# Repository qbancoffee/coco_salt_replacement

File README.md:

# Drop in replacement board for the custom SALT chip on the CoCo's

- [Installation instructions](https://github.com/qbancoffee/coco_salt_replacement/wiki/Installing-a-pepper-board)
- [View PDF version of the schematic](pepper_schematic.pdf)
- [Download the latest release](https://github.com/qbancoffee/coco_salt_replacement/releases/latest)
- [How to order from JLCPCB](#Ordering-the-board)
- [Peppers in the wild](#Peppers-In-The-Wild)

This board replaces the functionality of the SALT chip in the CoCo (CoCo 2 in my case). 
The SALT chip (Supply and Level Translator) is responsible for supply regulation, RS-232
interface, level translation, cassette read operations, and driving the cassette relay.

I designed it using available parts from JLCPCB to reduce assembly time and to bring down the cost.

## Goals
- [x] Power regulation with a switching regulator instead of a linear regulator.
- [x] RS232 interface.
- [x] Zero crossing detector to read cassette data.
- [x] Cassette relay control.

All goals were met!!!<br>
[Video testing the SALT replacement board AKA the PEPPER board](https://youtu.be/D6V6HFp6FHY)

## Layout

## 3D rendering and pictures of it installed

<br>
<br>

<br>
CoCo 2 with SALT chip top view rendering

<br>
CoCo 2 with SALT chip side view rendering

## SALT and PEPPER

## Ordering the board
First Thing to do is clone this repository or download the latest release.
- [Download the latest release](https://github.com/qbancoffee/coco_salt_replacement/releases/latest)<br>
All the files you'll need are in the gerber folder.

Many PCB manufacturers provide proprietary EDA software with nice and helpful features to help the user decrease the time and difficulty when designing a PCB. Unfortunately sometimes these programs will only allow you to order from that specific manufacturer. This is good for the manufacturer because it increases the odds that the person will order from them again because of the amount of time invested in learning to use that specific EDA program.

There are very nice EDA programs that will allow to design a PCB really quickly with fewer errors when it comes to components and footprints. Some of these programs are free to download and use for a trial period but after finishing your design sometimes you'll find that in order to export your design files so that you can actually order the boards you have to purchase a license. Sometimes you'll also find that there is a total area limit on the size of your design unless you buy a license. Companies use these tactics to make money and I really can't blame them because they have to make a living somehow.

I guess the question you might be asking is "Is there a specific PCB manufacturer I must use for a PCB designed with KiCAD?" The answer is no.
PCB manufacturers will still take your business even if you've elected to use another piece of software for your design so long as you can provide the Gerber files for your design. The Gerber format is an open ASCII vector format for printed circuit board (PCB) designs. It is the de facto standard used by PCB industry software to describe the printed circuit board images: copper layers, solder mask, legend, drill data, etc.

KiCAD has a bit of learning curve to it but once you are familiar with its quirks you'll find that having no limits on size, layers, components ect for your design is really nice and worth your investment in time. Also, being completely free, having no vendor association, and having no licensing issues  means that you can start using right it away without worries and when you're done just create the gerber files.

You can open the PCB design and create the gerber files yourself but I've already done that for the board so all you have to do is download the zip archive and upload it to your PCB manufacturer of choice. Click on the link below to download the gerber files.
<BR>
- [Download the gerber files for version 1](https://github.com/qbancoffee/coco_salt_replacement/raw/master/pepper_v1/salt_replacement/gerber/pepper_gerber.zip)
- [Download the gerber files for version 2](https://github.com/qbancoffee/coco_salt_replacement/raw/master/pepper_v2/salt_replacement/gerber/pepper_gerber_v2.zip)

There are a ton of PCB manufactures to choose from but recently I've been using [JLPCB](https://jlcpcb.com/) because the quality is good and they are well priced. JLPCB will even provide an automated online quote for pcb manufacturing and assembly. Once ordered they should arrive in the mail.
Obviously you can use any PCB manufacturer you wish.

Some manufacturers also have assembly services with costs varying based on the number of components, packaging and size of the board. 
Surface mount components are difficult to solder onto a board by hand but are perfect for automated PCB assembly making it much cheaper when it comes to using an assembly service. I chose to design these boards using surface mount components from LCSC's inventory so that JLCPCB can mostly assemble them.

To order the components you'll need a Bill Of Materials or a BOM. I've included a BOM for the board in the repo and just like the gerber files, they will be in the repo once you download it. Click on the link below to download the BOM.
<BR>
- [View BOM for the PEPPER board version 1](https://github.com/qbancoffee/coco_salt_replacement/blob/master/pepper_v1/salt_replacement/gerber/BOM.csv)
- [View BOM for the PEPPER board version 2](https://github.com/qbancoffee/coco_salt_replacement/blob/master/pepper_v2/salt_replacement/gerber/BOM.csv)

The BOM includes LCSC part numbers so you can order them from JLCPCB, manufacturer part numbers so can search for the parts sold by other vendors, and other nice pieces of information to help you along.

To assemble the board JLCPCB will need to know the part locations and orientations, this information is in the CPL file.
- [View the CPL file for version 1](https://github.com/qbancoffee/coco_salt_replacement/blob/master/pepper_v1/salt_replacement/gerber/salt_replacement-all-pos.csv)
- [View the CPL file for version 2](https://github.com/qbancoffee/coco_salt_replacement/blob/master/pepper_v2/salt_replacement/gerber/salt_replacement_v2-all-pos.csv) 

- Go to jlcpcb and create an account if you don't have one.
- Click on "Quote Now" and then click on "Add Gerber File"
- Select "pepper_gerber.zip"
- Scroll down and select "Free SMT Assembly for your PCB order"
- Select "Assemble Top side" and agree to the terms and conditions.
- Click on "Add BOM" and select "BOM.csv"
- Click on "Add CPL file" and select "salt_replacement-all-pos.csv"
- Click "Next" and go over the components and pricing.
- Click "Next" or "Save to Cart".
  
  If you like the price, order it and you should receive a mostly assembled board.
  
Beacuse they are through hole components you'll have to solder the pin headers yourself. However, I just found out that JLCPCB offers hand soldering services now so you may want to look into that.....
  
  If you don't have 2.54 mm pitch breakaway pin headers laying around you can order from many places.
  - Amazon
  - Digikey
  - Mouser
  
  Here is a machine pin version which works better for the different type of sockets out there.<br>
  https://www.ebay.com/itm/155119535147<br>
  Thanks for the suggestion RETRO Innovations!
    
  ## Peppers In The Wild
  [Junkman testing his pepper board](https://toobnix.org/w/trVFnngNR2Q8xo4Xgh9rEd)

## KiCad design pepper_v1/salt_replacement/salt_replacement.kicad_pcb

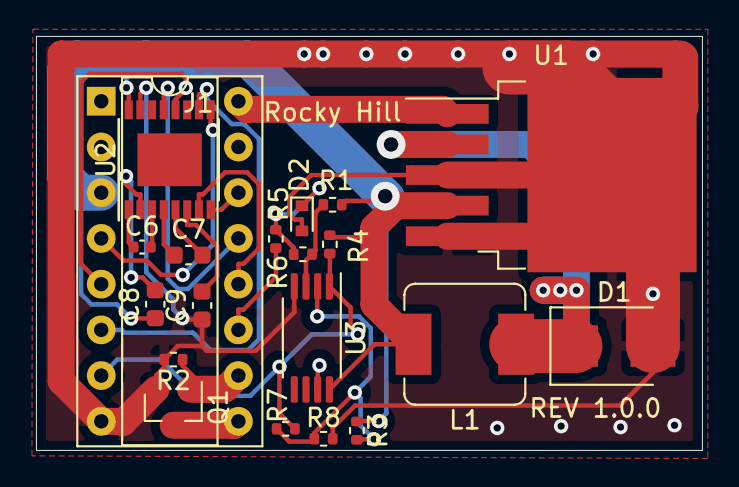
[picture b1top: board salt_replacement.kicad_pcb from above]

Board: 2 copper layers, 37.0 x 23.0 mm, 20 parts (0 on the bottom side), 23 nets.

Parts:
C6: .1uF; C_0402_1005Metric
C7, C8, C9: .47uF; C_0603_1608Metric
D1: 5A 40V; D_SMB
D2: 1N4148; D_SOD-523
J1: SALT chip package pins; DIP-16_W7.62mm_Socket
L1: 33uH; L_Sumida_CDMC6D28_7.25x6.5mm
Q1: MMBT9014C; SOT-23
R1, R3: 100K; R_0402_1005Metric
R2, R8: 10K; R_0402_1005Metric
R4, R5, R6: 5.1K; R_0402_1005Metric
R7: 20M; R_0402_1005Metric
U1: LM2596S-5; TO-263-5_TabPin3
U2: MAX3232; TSSOP-16-1EP_4.4x5mm_P0.65mm
U3: LM393; TSSOP-8_4.4x3mm_P0.65mm

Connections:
+5V: C8.1, J1.3, L1.2, R1.1, R3.1, R4.1, U1.4, U2.16, U3.8
/CASSETTE_DATA_IN: J1.11, R5.2
/CASSETTE_DATA_IN_TTL: J1.7, R4.2, R7.1, U3.1
/CD_IN_RS232: J1.13, U2.13
/CD_IN_TTL: J1.5, U2.12
/SERIAL_IN_RS232: J1.14, U2.8
/SERIAL_IN_TTL: J1.4, U2.9
/SERIAL_OUT_RS232: J1.12, U2.7
/SERIAL_OUT_TTL: J1.6, U2.10
GND: C9.1, D1.2, D2.2, J1.8, Q1.2, R2.2, R8.2, U1.3, U1.5, U2.15, U3.4
unnamed: C6.1, U2.1
unnamed: C6.2, U2.3
unnamed: C7.1, U2.4
unnamed: C7.2, U2.5
unnamed: C8.2, U2.2
unnamed: C9.2, U2.6
unnamed: D1.1, L1.1, U1.2
unnamed: D2.1, R5.1, R6.2
unnamed: J1.9, Q1.3
unnamed: J1.10, Q1.1, R2.1
unnamed: R1.2, R6.1, U3.3
unnamed: R3.2, R7.2, R8.1, U3.2
VCC: J1.16, U1.1

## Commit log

2021-05-07 -added more components -started making the PCB
2021-05-07 removed netlist files
2021-05-09 -complete redesign -replaced all components with jclpcb stock -added non-inverting zero crossing circuit.
2021-05-10 added
2021-05-10 added more images
2021-05-19 added some images
2021-05-19 rotated an image
2021-05-21 added zip archive with gerbers
2021-05-21 moved some columns around in the BOM
2021-05-21 Update README.md
    Added instructions to order the boards with assembly from JLCPCB
2021-05-21 fixed gerber
2021-05-25 added gnu licesnse file
2021-11-23 updated BOM with available parts from jlcpcb
2022-05-15 cleaned up schematic, added comments and added a PDF version of the schematic
2022-10-04 added a second version of the pepper board
2023-03-19 added some images for the wiki
2023-03-19 updated some of the images
